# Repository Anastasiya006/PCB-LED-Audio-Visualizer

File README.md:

# PCB LED Audio Visualizer
https://github.com/user-attachments/assets/34dc9e85-68ce-4a28-94b5-732c458a7c48

## Overview
A custom audio visualizer printed circuit board (PCB), designed using KiCad and programmed with Arduino and C++, featuring interrupt-driven C++ logic to synchronize RGB LED animations with real-time audio dynamics. This design processes audio signals and displays dynamic patterns onto two 8x8 RGB LED matrices.

## Components
- **Arduino Mega 2560**: microcontroller for processing audio signals and controlling the LED matrix
- **Custom PCB**: custom-designed printed circuit board shield for Arduino
- **8x8 RGB LED Matrix**: dynamic visualization of audio signals
- **3.5mm Audio Jack**: allows for audio input from external devices

## Design
### Circuit Schematic

### PCB Layout & Routing

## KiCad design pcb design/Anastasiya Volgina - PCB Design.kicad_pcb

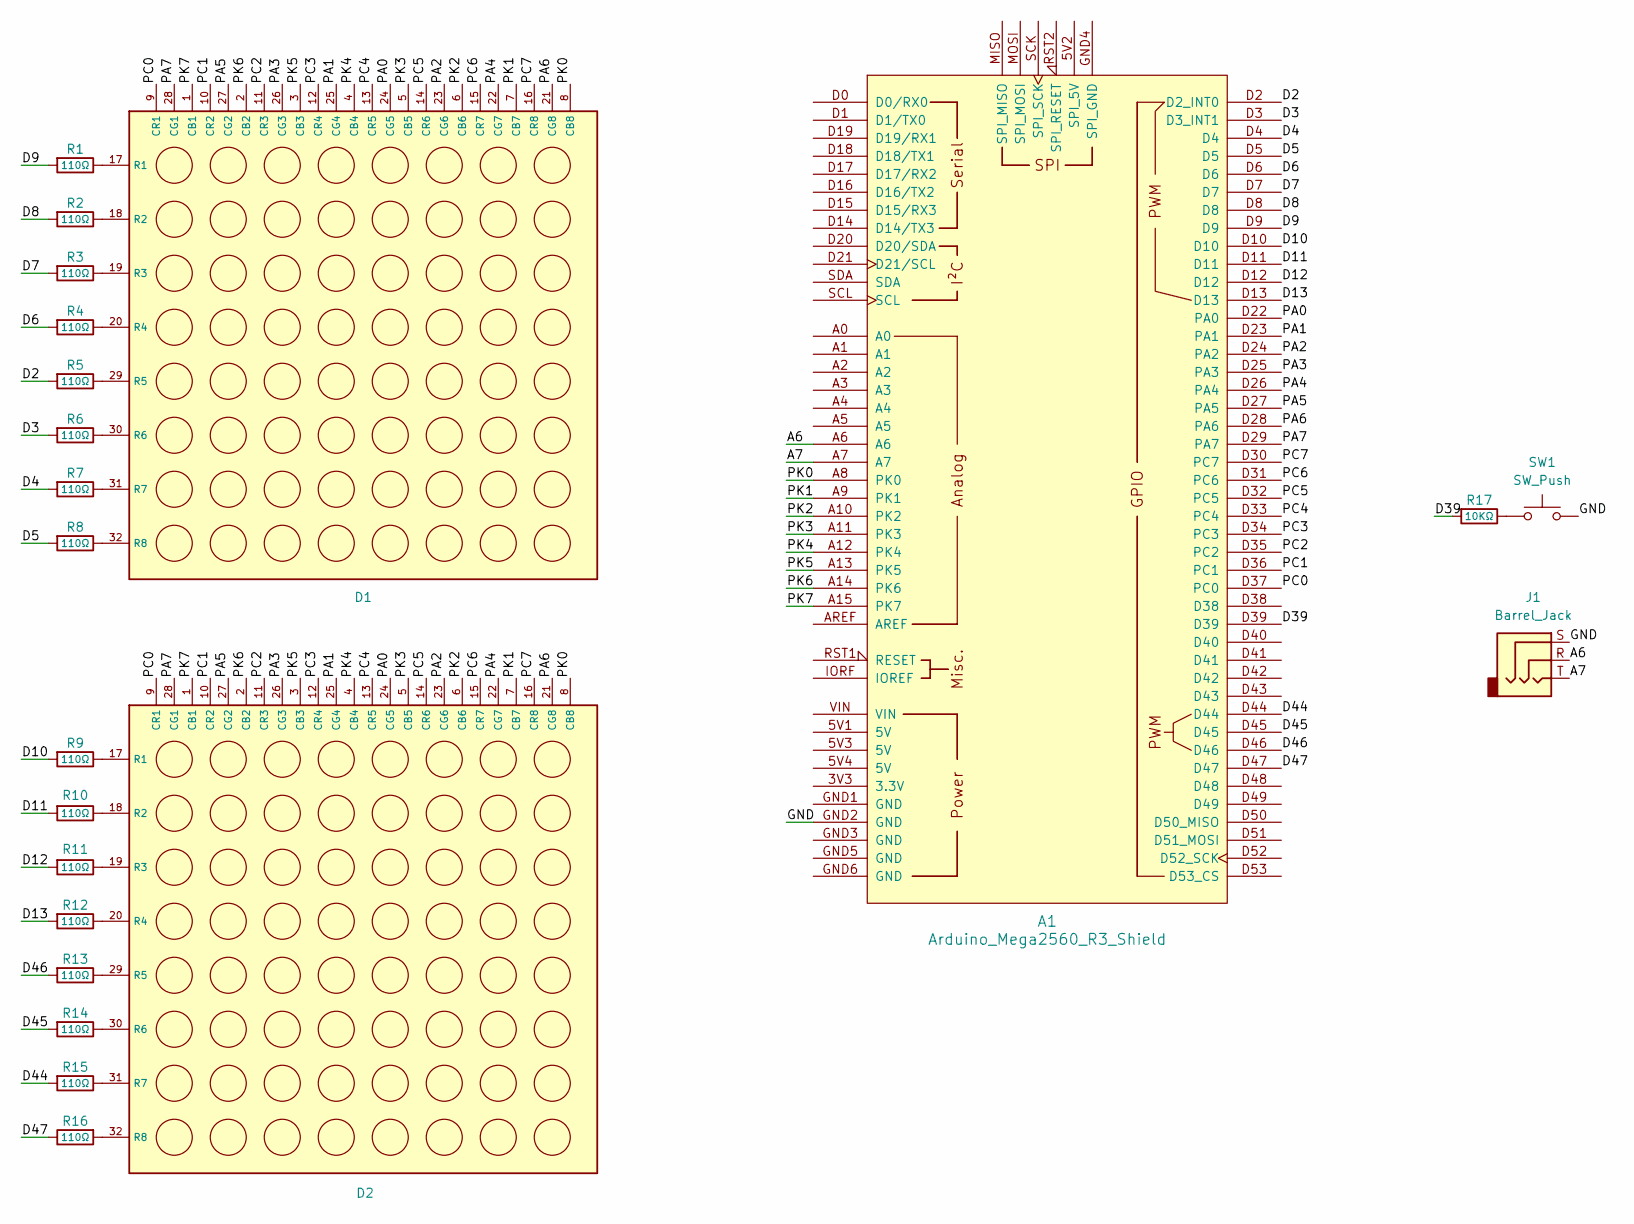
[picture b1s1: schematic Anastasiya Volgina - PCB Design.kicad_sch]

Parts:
A1: Arduino_Mega2560_R3_Shield
D1, D2: ORM-2388ARGB-L
J1: Barrel_Jack; Jack_3.5mm_CUI_SJ-3523-SMT_Horizontal
R1, R2, R3, R4, R5, R6, R7, R8, R9, R10, R11, R12, R13, R14, R15, R16: 110Ω; R_Axial_DIN0204_L3.6mm_D1.6mm_P5.08mm_Horizontal
R17: 10KΩ; R_Axial_DIN0204_L3.6mm_D1.6mm_P5.08mm_Horizontal
SW1: SW_Push; SW_1825910-6-4

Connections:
/A6: A1.A6, J1.R
/A7: A1.A7, J1.T
/A8: A1.A8 (PK0), D1.8 (CB8), D2.8 (CB8)
/A9: A1.A9 (PK1), D1.7 (CB7), D2.7 (CB7)
/A10: A1.A10 (PK2), D1.6 (CB6), D2.6 (CB6)
/A11: A1.A11 (PK3), D1.5 (CB5), D2.5 (CB5)
/A12: A1.A12 (PK4), D1.4 (CB4), D2.4 (CB4)
/A13: A1.A13 (PK5), D1.3 (CB3), D2.3 (CB3)
/A14: A1.A14 (PK6), D1.2 (CB2), D2.2 (CB2)
/A15: A1.A15 (PK7), D1.1 (CB1), D2.1 (CB1)
/D2: A1.D2 (D2_INT0), R5.2
/D3: A1.D3 (D3_INT1), R6.2
/D4: A1.D4, R7.2
/D5: A1.D5, R8.2
/D6: A1.D6, R4.2
/D7: A1.D7, R3.2
/D8: A1.D8, R2.2
/D9: A1.D9, R1.2
/D10: A1.D10, R9.2
/D11: A1.D11, R10.2
/D12: A1.D12, R11.2
/D13: A1.D13, R12.2
/D22: A1.D22 (PA0), D1.24 (CG5), D2.24 (CG5)
/D23: A1.D23 (PA1), D1.25 (CG4), D2.25 (CG4)
/D24: A1.D24 (PA2), D1.23 (CG6), D2.23 (CG6)
/D25: A1.D25 (PA3), D1.26 (CG3), D2.26 (CG3)
/D26: A1.D26 (PA4), D1.22 (CG7), D2.22 (CG7)
/D27: A1.D27 (PA5), D1.27 (CG2), D2.27 (CG2)
/D28: A1.D28 (PA6), D1.21 (CG8), D2.21 (CG8)
/D29: A1.D29 (PA7), D1.28 (CG1), D2.28 (CG1)
/D30: A1.D30 (PC7), D1.16 (CR8), D2.16 (CR8)
/D31: A1.D31 (PC6), D1.15 (CR7), D2.15 (CR7)
/D32: A1.D32 (PC5), D1.14 (CR6), D2.14 (CR6)
/D33: A1.D33 (PC4), D1.13 (CR5), D2.13 (CR5)
/D34: A1.D34 (PC3), D1.12 (CR4), D2.12 (CR4)
/D35: A1.D35 (PC2), D1.11 (CR3), D2.11 (CR3)
/D36: A1.D36 (PC1), D1.10 (CR2), D2.10 (CR2)
/D37: A1.D37 (PC0), D1.9 (CR1), D2.9 (CR1)
/D39: A1.D39, R17.2
/D44: A1.D44, R15.2
/D45: A1.D45, R14.2
/D46: A1.D46, R13.2
/D47: A1.D47, R16.2
/GND: A1.GND2 (GND), J1.S, SW1.2
unnamed: D1.17 (R1), R1.1
unnamed: D1.18 (R2), R2.1
unnamed: D1.19 (R3), R3.1
unnamed: D1.20 (R4), R4.1
unnamed: D1.29 (R5), R5.1
unnamed: D1.30 (R6), R6.1
unnamed: D1.31 (R7), R7.1
unnamed: D1.32 (R8), R8.1
unnamed: D2.17 (R1), R9.1
unnamed: D2.18 (R2), R10.1
unnamed: D2.19 (R3), R11.1
unnamed: D2.20 (R4), R12.1
unnamed: D2.29 (R5), R13.1
unnamed: D2.30 (R6), R14.1
unnamed: D2.31 (R7), R15.1
unnamed: D2.32 (R8), R16.1
unnamed: R17.1, SW1.1

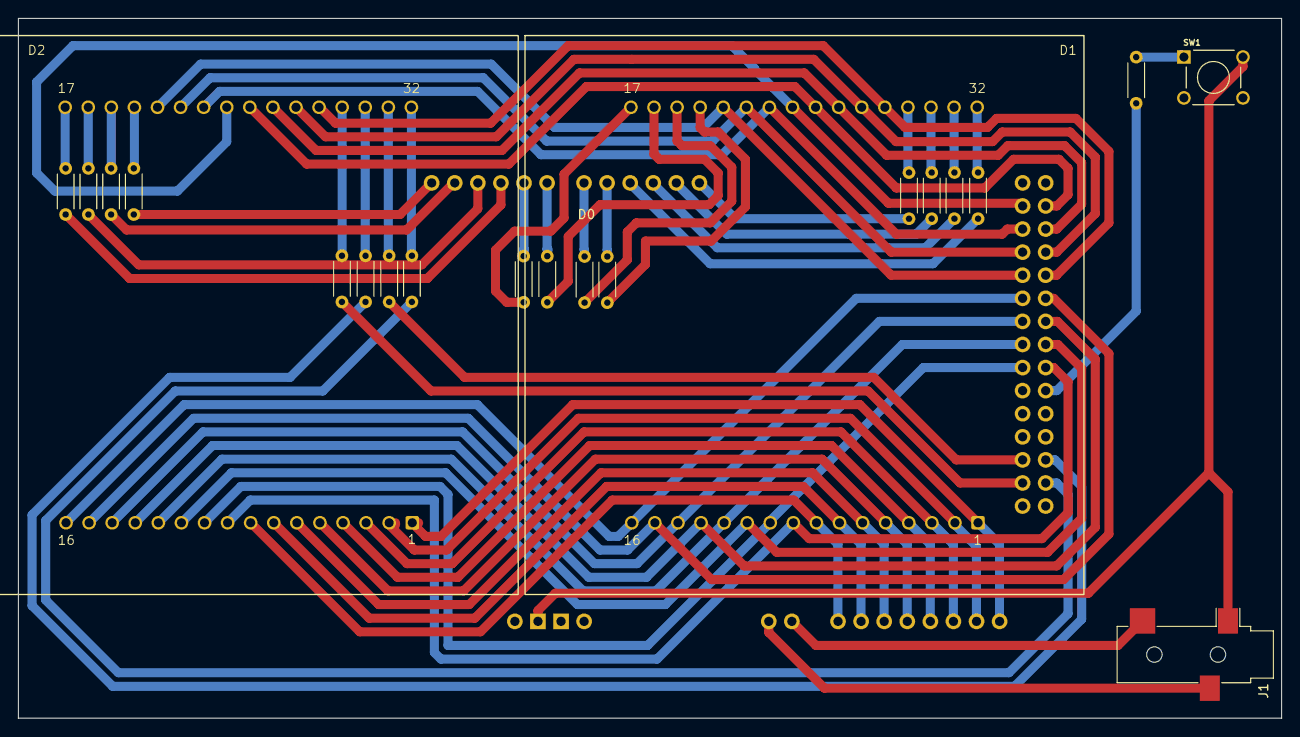
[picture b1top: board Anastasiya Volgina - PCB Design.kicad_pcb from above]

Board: 2 copper layers, 139.0 x 77.0 mm, 22 parts (0 on the bottom side), 61 nets.

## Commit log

2025-01-05 Arduino Code
2025-01-05 PCB Design
